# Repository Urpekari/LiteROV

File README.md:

# LiteROV

ROV arina hezkuntza erabilererarako. 3 motore, dual H-Bridge kontroladorea eta JoyC mandoaz erabiltzeko.

Light ROV system for educational purposes. 3 Motors, dual H-Bridge drive and JoyC Controls.

ROV ligero para fines educativos. Pensado para funcionar con 3 motores, controlador dual H-Bridge y mando JoyC.

## Authors

**Urpekari Proiektua - 2024**

EHU - Bilboko ingeniaritza eskola¡

University of the Basque Country - Bilbao school of engineering

UPV - Escuela de ingeinería de Bilbao

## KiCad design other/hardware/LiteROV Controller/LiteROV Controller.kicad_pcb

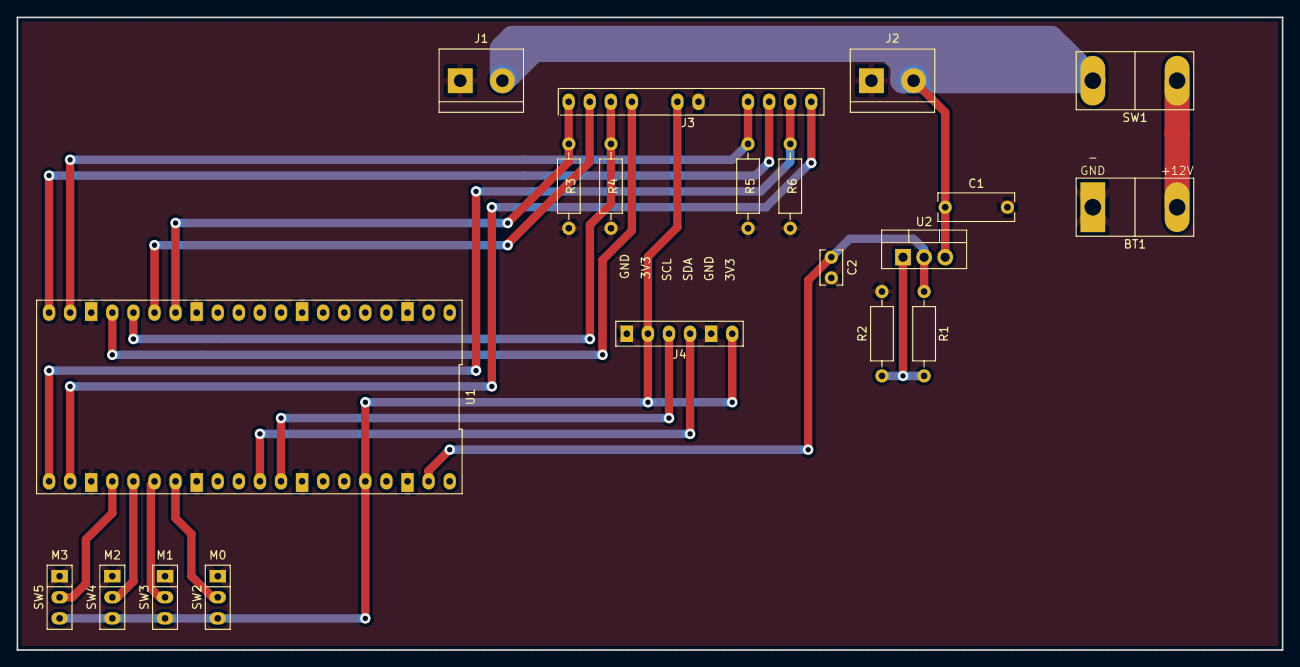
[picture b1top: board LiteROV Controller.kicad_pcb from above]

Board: 2 copper layers, 152.4 x 76.2 mm, 20 parts (0 on the bottom side), 20 nets.

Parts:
BT1: 12V; BATTERY-CABLE
C1: 1µF; C_Rect_L9.0mm_W3.2mm_P7.50mm_MKT
C2: 0.1µF; C_Rect_L4.0mm_W2.5mm_P2.50mm
J1, J2: Screw; TerminalBlock_bornier-2_P5.08mm
J3: CONT-CONN
J4: JOYC-CONN
R1: 240R; R_Axial_DIN0207_L6.3mm_D2.5mm_P10.16mm_Horizontal
R2: 750R; R_Axial_DIN0207_L6.3mm_D2.5mm_P10.16mm_Horizontal
R3, R4, R5, R6: 330R; R_Axial_DIN0207_L6.3mm_D2.5mm_P10.16mm_Horizontal
SW1: SW_SPST; POWER-CABLE
SW2, SW3, SW4, SW5: SW_SPDT; SERVO
U1: RPI-PICO
U2: LM317_TO-220; TO-220-3_Vertical

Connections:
3V3: J3.5, J4.2, J4.6, SW2.3 (C), SW3.3 (C), SW4.3 (C), SW5.3 (C), U1.36 (3V3(OUT))
5VREG: C2.1, R1.1, U1.39 (VSYS), U2.2 (VO)
DIR_SET_0 PULLUP: SW2.2 (B), U1.27 (GPIO_21)
DIR_SET_1 PULLUP: SW3.2 (B), U1.26 (GPIO_20)
DIR_SET_2 PULLUP: SW4.2 (B), U1.25 (GPIO_19)
DIR_SET_3 PULLUP: SW5.2 (B), U1.24 (GPIO_18)
GND: BT1.2 (-), C1.2, C2.2, J1.1, J2.1, J3.6, J4.1, J4.5, R2.2, R3.2, R4.2, R5.2, R6.2, SW2.1 (A), SW3.1 (A), SW4.1 (A), SW5.1 (A), U1.3 (GND), U1.8 (GND), U1.13 (GND), U1.18 (GND), U1.23 (GND), U1.28 (GND), U1.33 (GND), U1.38 (GND)
MOT_0_DIR: J3.2, U1.15 (GPIO_11)
MOT_0_PWM: J3.1, R3.1, U1.14 (GPIO_10)
MOT_1_DIR: J3.4, U1.17 (GPIO_13)
MOT_1_PWM: J3.3, R4.1, U1.16 (GPIO_12)
MOT_2_DIR: J3.8, U1.20 (GPIO_15)
MOT_2_PWM: J3.7, R5.1, U1.19 (GPIO_14)
MOT_3_DIR: J3.10, U1.22 (GPIO_17)
MOT_3_PWM: J3.9, R6.1, U1.21 (GPIO_16)
unnamed: BT1.1 (+), SW1.1 (A)
unnamed: C1.1, J1.2, J2.2, SW1.2 (B), U2.3 (VI)
unnamed: R1.2, R2.1, U2.1 (ADJ)
SCL: J4.3, U1.32 (GPIO_27)
SDA: J4.4, U1.31 (GPIO_26)

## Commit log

2024-06-19 Basic single-motor functions implemented
2024-06-20 LiteROV v1.0
    The basic functions are there, it may require a bit of polishing but it should work.
    It will be tested with the actual motors on 2024-06-21
2024-07-11 Added schematics, PCB design
2024-07-11 Create LICENSE
    Hard Open Source License
2024-07-11 Datasheet start
    Preliminary version of the datasheet and manual document
2024-07-12 directory cleanup
2024-07-12 Clearup notes
    Notes added regarding the usage of the SERVO library and its modifications.
